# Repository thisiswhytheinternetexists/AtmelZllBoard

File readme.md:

# Atmel Zigbee Light Link demo LED board
A board that should be able to connect to a ZLL-enabled network (Philips Hue?) and function as both a color LED and a router for the network.

Includes a library for the ATSAMR21B18-MZ210PA for Eagle.

# Used Libraries/code:
https://github.com/NBitWonder/NBitWonder-Eagle-Library
http://www.atmel.com/tools/BITCLOUD-ZIGBEEPRO.aspx

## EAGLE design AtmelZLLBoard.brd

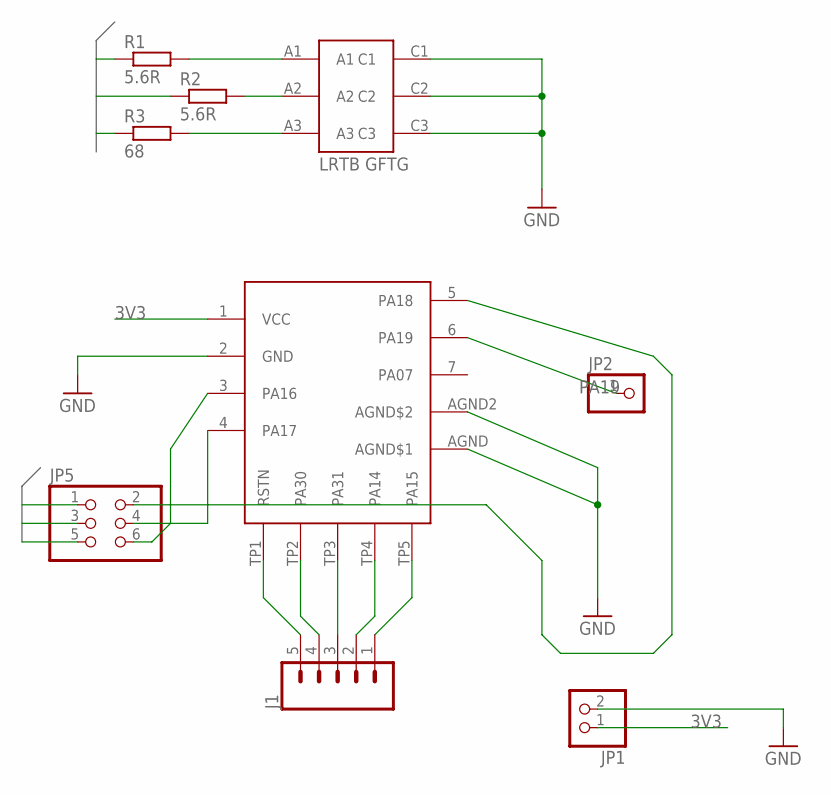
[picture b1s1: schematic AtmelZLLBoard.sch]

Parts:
J1: CONN_05LOCK; 1X05_LOCK
JP1: PINHD-1X2; 1X02
JP2: PINHD-1X1; 1X01
JP5: PINHD-2X3; 2X03
R1, R2: 5.6R; 0204/5
R3: 68; 0204/5
U$1: ATSAMR21B18-MZ210PA-DEV
U$2: LRTB_GFTG

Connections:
3V3: JP1.1, U$1.1 (VCC)
B: JP5.1, R1.1
G: JP5.3, R2.1
GND: JP1.2, U$1.2 (GND), U$1.AGND (AGND$1), U$1.AGND2 (AGND$2), U$2.C1, U$2.C2, U$2.C3
unnamed: J1.5, U$1.TP1 (RSTN)
unnamed: R1.2, U$2.A1
unnamed: R2.2, U$2.A2
unnamed: R3.2, U$2.A3
unnamed: JP5.4, U$1.4 (PA17)
unnamed: JP5.2, U$1.5 (PA18)
unnamed: JP5.6, U$1.3 (PA16)
unnamed: J1.4, U$1.TP2 (PA30)
unnamed: J1.3, U$1.TP3 (PA31)
unnamed: J1.2, U$1.TP4 (PA14)
unnamed: J1.1, U$1.TP5 (PA15)
PA19: JP2.1, U$1.6 (PA19)
R: JP5.5, R3.1

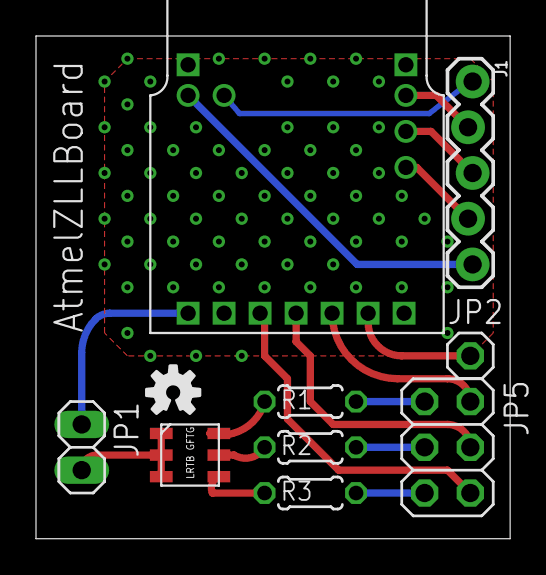
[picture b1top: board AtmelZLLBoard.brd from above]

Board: 2 copper layers, 26.3 x 27.9 mm, 11 parts (1 on the bottom side), 17 nets.

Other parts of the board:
U$3: OSHW-LOGO-S
U$4: TIWTIE_LOGO

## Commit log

2016-07-05 Added atmel-zll lbrary file for the Atmel module with package, device and symbol. Added the version of the ZLLBoard that is sent to OSHPark. Also included the datasheets for the "special" components 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
2016-07-21 Replaced resistors
2016-07-21 Rewired stuff, added extra via's. Changed board dimensions.
2017-01-29 Update the "DEV" part so it actually includes the test points in the footprint
2017-01-29 Replaced the regalar module with the module that contains the dev pads. Decreased the pad size, added oshpark rules for DRC. Added extra header onto the board that routes the programming pins.

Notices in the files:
parts and their libraries:
SparkFun-Connectors: Licensing: Creative Commons ShareAlike 4.0 International - https://creativecommons.org/licenses/by-sa/4.0
